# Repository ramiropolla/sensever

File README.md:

sensever
========

O projeto consiste em 17 tablados com sensores piezo-elétricos.

<pre>
      Esquemático dos tablados
                _____
               /     \
         _____/   5   \_____
        /     \       /     \
       /  13   \_____/   9   \
       \       /     \       /
        \_____/   4   \_____/
        /     \       /     \
  _____/  12   \_____/   8   \_____
 /     \       /     \       /     \
/  17   \_____/   3   \_____/  15   \
\       /     \       /     \       /
 \_____/  11   \_____/   7   \_____/
 /     \       /     \       /     \
/  16   \_____/   2   \_____/  14   \
\       /     \       /     \       /
 \_____/  10   \_____/   6   \_____/
       \       /     \       /
        \_____/   1   \_____/
              \       /
               \_____/
</pre>

A leitura dos sensores é feita com 4 placas Arduino distribuidas entre os
tablados. Os Arduinos estão nas placas 2, 4, 14 e 16, de forma a otimizar
o caminho de comunicação do circuito. A placa de número 4 está ligada pela
USB ao PC que controla o circuito. A placa 4 também está ligada à placa 2,
que por sua vez está ligada às placas 14 e 16.

<pre>
Esquemático de comunicação dos Arduinos
    ______
   |      |
   |  PC  |
   |______|
           \    _____
            \  /     \
         ____\/   5   \_____
        /     \       /     \
       /  13   \_____/   9   \
       \       /\_   \       /
        \_____/   4   \_____/
        /     \   |   /     \
  _____/  12   \__|__/   8   \_____
 /     \       /  |  \       /     \
/  17   \_____/   3   \_____/  15   \
\       /     \   |   /     \       /
 \_____/  11   \__|__/   7   \_____/
 /     \       /  |  \       /     \
/  16__ \_____/   2   \_____/ _14   \
\      \/     \__/ \__/     \/      /
 \_____/\_10__/\_____/\__6__/\_____/
       \       /     \       /
        \_____/   1   \_____/
              \       /
               \_____/
</pre>

Para evitar que o ruído da rede elétrica influencie na leitura dos sensores
piezo-elétricos, é utilizado um circuito opto-isolador na placa 4. Assim,
a placa 4 tem um cabo denominado 'PC', que deve ser ligado ao computador,
e outro cabo denominado 'Tomada', que deve ser ligado em alguma fonte USB
que não apresente ruído, como um Power Bank USB ou um computador com a
bateria carregada e que não esteja ligado na tomada.

Cada sensor piezo-elétrico está ligado ao Arduino mais próximo.

No Arduino 2 estão ligadas as placas 1, 3, 6, 7, 10 e 11.

No Arduino 4 estão ligadas as placas 5, 8, 9, 12 e 13.

No Arduino 14 está ligada a placa 15.

No Arduino 16 está ligada a placa 17.

<pre>
 Esquemático de sensores por Arduino
                _____
               /     \
         _____/   5   \_____
        /     \   |   /     \
       /  13__ \__|__/ __9   \
       \      \/  |  \/      /
        \_____/\__4__/\_____/
        /     \/     \/     \
  _____/  12__/\_____/\__8   \_____
 /     \       /     \       /     \
/  17   \_____/   3   \_____/  15   \
\   |   /     \   |   /     \   |   /
 \__|__/  11__ \__|__/ __7   \__|__/
 /  |  \      \/  |  \/      /  |  \
/  16   \_____/\__2__/\_____/  14   \
\       /     \/  |  \/     \       /
 \_____/  10__/\__|__/\__6   \_____/
       \       /  |  \       /
        \_____/   1   \_____/
              \       /
               \_____/
</pre>

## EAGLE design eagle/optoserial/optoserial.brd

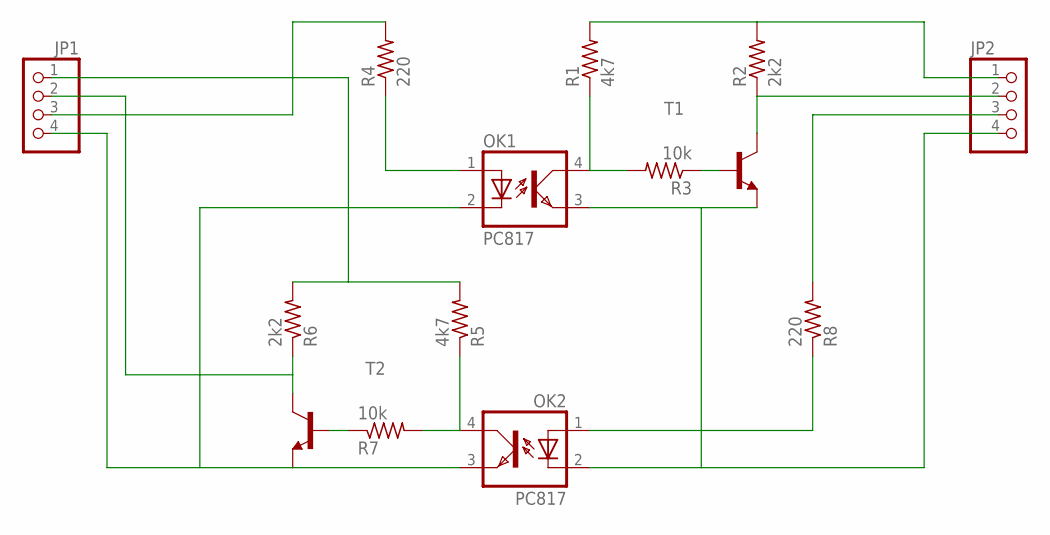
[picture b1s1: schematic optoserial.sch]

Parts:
JP1, JP2: PINHD-1X4; 1X04
OK1, OK2: PC817; DIL04
R1, R5: 4k7; 0207/10
R2, R6: 2k2; 0207/10
R3, R7: 10k; 0207/10
R4, R8: 220; 0207/10
T1, T2: 2N2222-NPN-TO92-EBC; TO92-EBC

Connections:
unnamed: JP2.1, R1.2, R2.2
unnamed: OK1.4 (COL), R1.1, R3.2
unnamed: JP2.4, OK1.3 (EMIT), OK2.2 (C), T1.E
unnamed: R3.1, T1.B
unnamed: JP2.2, R2.1, T1.C
unnamed: OK1.1 (A), R4.1
unnamed: JP1.1, R5.2, R6.2
unnamed: OK2.4 (COL), R5.1, R7.2
unnamed: JP1.4, OK1.2 (C), OK2.3 (EMIT), T2.E
unnamed: R7.1, T2.B
unnamed: JP1.2, R6.1, T2.C
unnamed: OK2.1 (A), R8.1
unnamed: JP1.3, R4.2
unnamed: JP2.3, R8.2

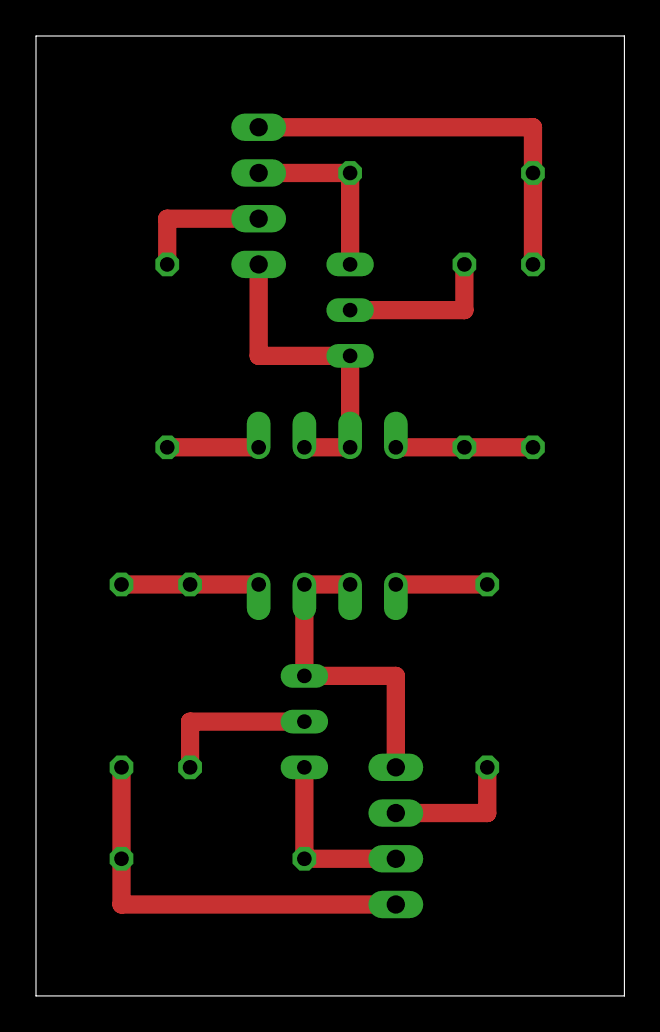
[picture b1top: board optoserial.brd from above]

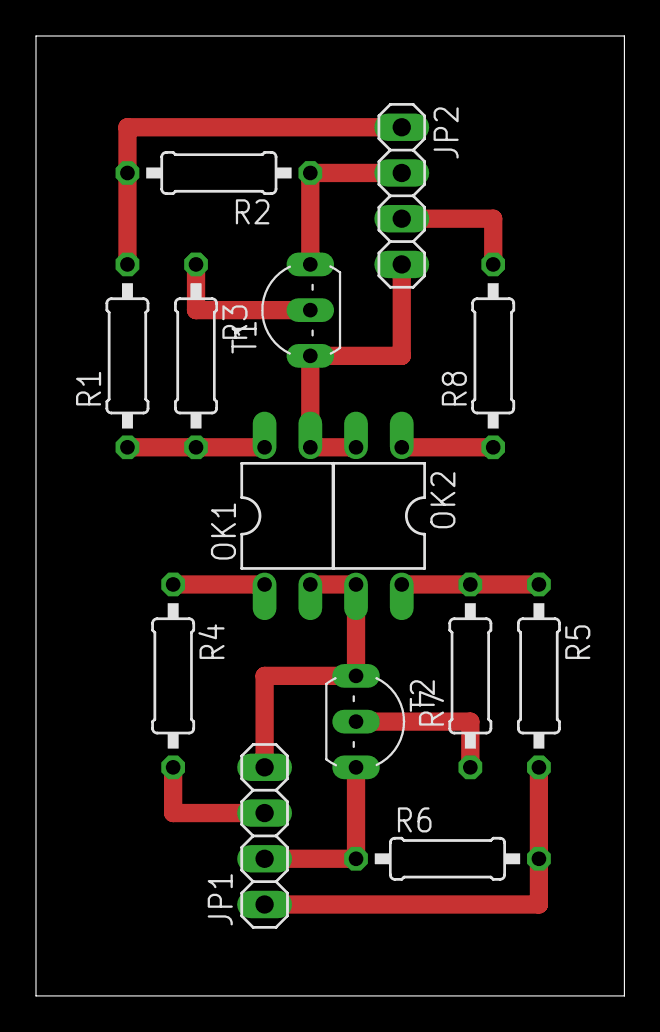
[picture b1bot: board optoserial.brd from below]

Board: 2 copper layers, 32.7 x 53.3 mm, 14 parts (14 on the bottom side), 14 nets.

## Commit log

2013-12-11 sketchbook: commit inicial
2014-05-28 atualizar arquivos de arduino
2014-05-28 sketchbook -> arduino
2014-05-28 processing: adicionar
2014-05-28 processing: adicionar teste_sensever
2014-05-28 optoserial: adicionar esquemáticos do eagle
2014-05-28 adicionar explicação dos arduinos
